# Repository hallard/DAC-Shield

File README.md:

0-10V DAC / ADC / RS485 and OLED Arduino Shield
===============================================

This is a simple board to be able to 
- Generate 4 0-10V analog output to drive industrial devices
- 2 0-10V analog input (unprotected) 
- A RS485 Driver (use RX/TX of Arduino)
- 2 I2C Oled connector (Adafruit or Tindie Oled)
- 1 Rotary Encoder
- 1 WS2812B RGB Led

<strike>This is a proto board, I've just ordered one on OSHPark, will put 
more details once received and tested</strike> This shield has been fully tested and it's working fine on all features. 
The only problem was my bad datasheet reading, the DAC7565 output from the chip are not 0V 5V as I expected but 0V 2.5V (internal VREF) So as I multiply ouput per 2, the output for these 4 outputs are 0V-5V not 0V-10V, you can change the multiplier by changing resitor R2/R4/R6/R8 from 10K to 30K.
Also TL072 are not working well with single rail supply for PWM to DAC conversion at low level (says from 0V to 1V), I replaced them
by LM358 (same package) but more suited for single rail supply.

I wrote an Arduino Library to drive the DAC7565 [here][3]

Check out news and other projects on my [blog][4]

Detailed Description
====================

Everything will be documented on my [blog][4]

**Schematic**  

**Board**  

&nbsp;&nbsp;

[3]: https://github.com/hallard/DAC7565
[4]: http://hallard.me

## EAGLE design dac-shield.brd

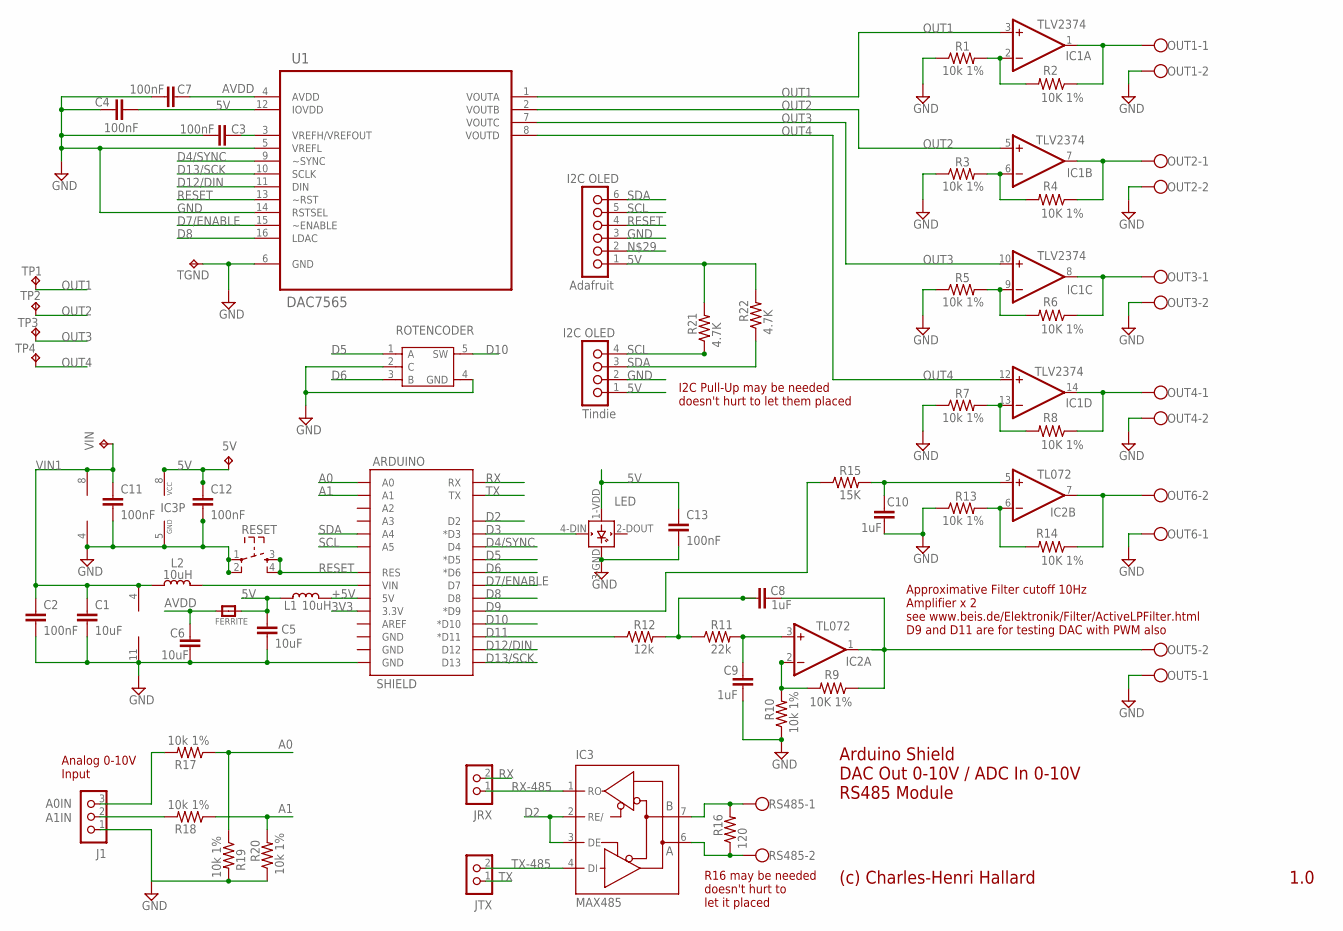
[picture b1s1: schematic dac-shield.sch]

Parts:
5V: TPPAD1-13; P1-13
ARDUINO: SHIELD; DUEMILANOVE_SHIELD_NOHOLES
C1, C5, C6: 10uF; 0805-CAP
C2, C3, C4, C7, C11, C12, C13: 100nF; 0805-CAP
C8, C9, C10: 1uF; 0805-CAP
FERRITE: FERRITE_0603; _0603
IC1: TLV2374; SO14
IC2: TL072; SO08
IC3: MAX485; SO08
J1: CON_HEADER_1X03-PTH; M1X3
JRX: CON_HEADER_1X02-PTH; M1X2
JTX: CON_HEADER_1X02-PTH; M1X2
L1, L2: 10uH; _0805
LED: WS2812B
OUT1, OUT2, OUT3, OUT4, OUT5, OUT6: CON-CLAMP-2; W237-102
R1, R3, R5, R7, R10, R13, R17, R18, R19, R20: 10k 1%; 0805-RES
R2, R4, R6, R8, R9, R14: 10K 1%; 0805-RES
R11: 22k; 0805-RES
R12: 12k; 0805-RES
R15: 15K; 0805-RES
R16: 120; 0805-RES
R21, R22: 4.7K; 0805-RES
RESET: SW_TACT_4P; SW_TACT_SMALL
ROTENCODER: ROTARY-ENCODE-5P; 5P-13.75X11.7X6.5H
RS485: CON-CLAMP-2; W237-102
TGND: TPPAD1-13; P1-13
TP1, TP2, TP3, TP4: TPPAD1-13; P1-13
U1: DAC7565; SOP65P640X120-16N
U$1: OLED_I2C_ADAFRUIT; 1X06_LOCK
U$2: OLED_I2C_TINDIE; 1X04_LOCK
VIN: TPPAD1-13; P1-13

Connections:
3V3: ARDUINO.3.3V
5V: 5V.TP, C4.1, C5.1, C12.1, C13.1, FERRITE.1, IC3.8 (VCC), L1.1, LED.1-VDD (VDD), R21.2, R22.2, U1.12 (IOVDD), U$1.1 (VIN), U$2.1 (VCC)
+5V: ARDUINO.5V, L1.2
A0: ARDUINO.A0, R17.1, R19.1
A0IN: J1.3, R17.2
A1: ARDUINO.A1, R18.1, R20.2
A1IN: J1.2, R18.2
AVDD: C6.2, C7.1, FERRITE.2, U1.4 (AVDD)
D2: ARDUINO.D2, IC3.2 (RE/), IC3.3 (DE)
D3: ARDUINO.D3 (*D3), LED.4-DIN (DIN)
D4/SYNC: ARDUINO.D4, U1.9 (~SYNC)
D5: ARDUINO.D5 (*D5), ROTENCODER.1 (A)
D6: ARDUINO.D6 (*D6), ROTENCODER.3 (B)
D7/ENABLE: ARDUINO.D7, U1.15 (~ENABLE)
D8: ARDUINO.D8, U1.16 (LDAC)
D9: ARDUINO.D9 (*D9), R15.1
D10: ARDUINO.D10 (*D10), ROTENCODER.5 (SW)
D11: ARDUINO.D11 (*D11), R12.1
D12/DIN: ARDUINO.D12, U1.11 (DIN)
D13/SCK: ARDUINO.D13, U1.10 (SCLK)
GND: ARDUINO.GND@0 (GND), C1.2, C2.2, C3.2, C4.2, C5.2, C6.1, C7.2, C9.1, C10.1, C11.2, C12.2, C13.2, IC1.11 (V-), IC2.4 (V-), IC3.5 (GND), J1.1, LED.3-GND (GND), OUT1.2, OUT2.2, OUT3.2, OUT4.2, OUT5.1, OUT6.1, R1.1, R3.1, R5.1, R7.1, R10.1, R13.1, R19.2, R20.1, RESET.1, RESET.2, ROTENCODER.2 (C), ROTENCODER.4 (GND), TGND.TP, U1.5 (VREFL), U1.6 (GND), U1.14 (RSTSEL), U$1.3 (GND), U$2.2 (GND)
unnamed: IC1.6 (-IN), R3.2, R4.2
unnamed: IC1.2 (-IN), R1.2, R2.2
unnamed: IC1.1 (OUT), OUT1.1, R2.1
unnamed: ARDUINO.VIN, L2.2
unnamed: IC2.2 (-IN), R9.2, R10.2
unnamed: C3.1, U1.3 (VREFH/VREFOUT)
unnamed: IC2.6 (-IN), R13.2, R14.2
unnamed: C8.2, IC2.1 (OUT), OUT5.2, R9.1
unnamed: IC1.7 (OUT), OUT2.1, R4.1
unnamed: IC1.9 (-IN), R5.2, R6.2
unnamed: IC1.8 (OUT), OUT3.1, R6.1
unnamed: IC1.13 (-IN), R7.2, R8.2
unnamed: IC1.14 (OUT), OUT4.1, R8.1
unnamed: C8.1, R11.1, R12.2
unnamed: C9.2, IC2.3 (+IN), R11.2
unnamed: IC2.7 (OUT), OUT6.2, R14.1
unnamed: C10.2, IC2.5 (+IN), R15.2
unnamed: IC3.7 (B), R16.2, RS485.1
unnamed: IC3.6 (A), R16.1, RS485.2
OUT1: IC1.3 (+IN), TP1.TP, U1.1 (VOUTA)
OUT2: IC1.5 (+IN), TP2.TP, U1.2 (VOUTB)
OUT3: IC1.10 (+IN), TP3.TP, U1.7 (VOUTC)
OUT4: IC1.12 (+IN), TP4.TP, U1.8 (VOUTD)
RESET: ARDUINO.RES, RESET.3, RESET.4, U1.13 (~RST), U$1.4 (RST)
RX: ARDUINO.RX, JRX.2
RX-485: IC3.1 (RO), JRX.1
SCL: ARDUINO.A5, R21.1, U$1.5 (SCL), U$2.4 (SCL)
SDA: ARDUINO.A4, R22.1, U$1.6 (SDA), U$2.3 (SDA)
TX: ARDUINO.TX, JTX.1
TX-485: IC3.4 (DI), JTX.2
VIN1: C1.1, C2.1, C11.1, IC1.4 (V+), IC2.8 (V+), L2.1, VIN.TP

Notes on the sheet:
Approximative Filter cutoff 10Hz Amplifier x 2 see www.beis.de/Elektronik/Filter/ActiveLPFilter.html D9 and D11 are for testing DAC with PWM also
I2C Pull-Up may be needed doesn't hurt to let them placed
Analog 0-10V Input
(c) Charles-Henri Hallard
1.0
Arduino Shield DAC Out 0-10V / ADC In 0-10V RS485 Module
R16 may be needed doesn't hurt to let it placed

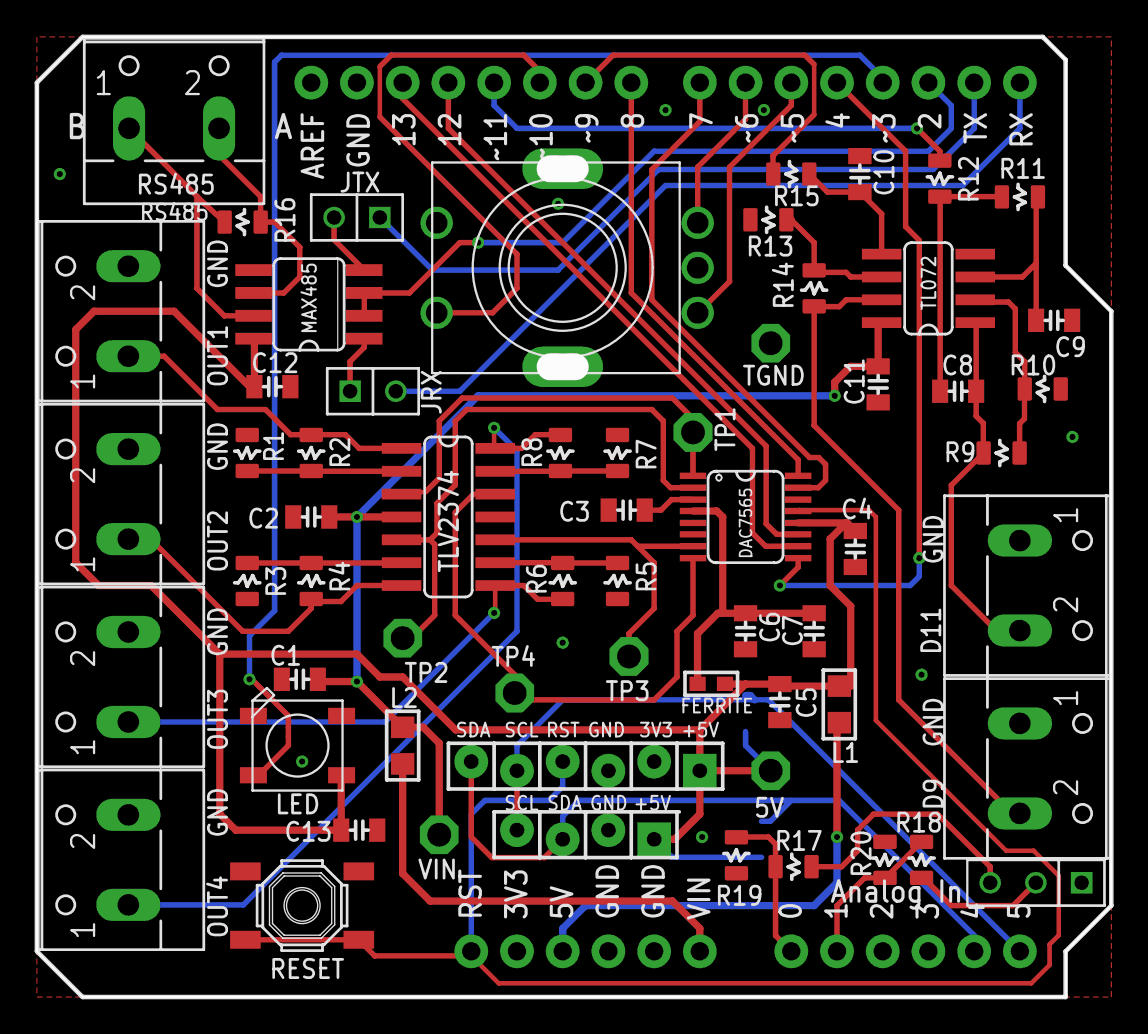
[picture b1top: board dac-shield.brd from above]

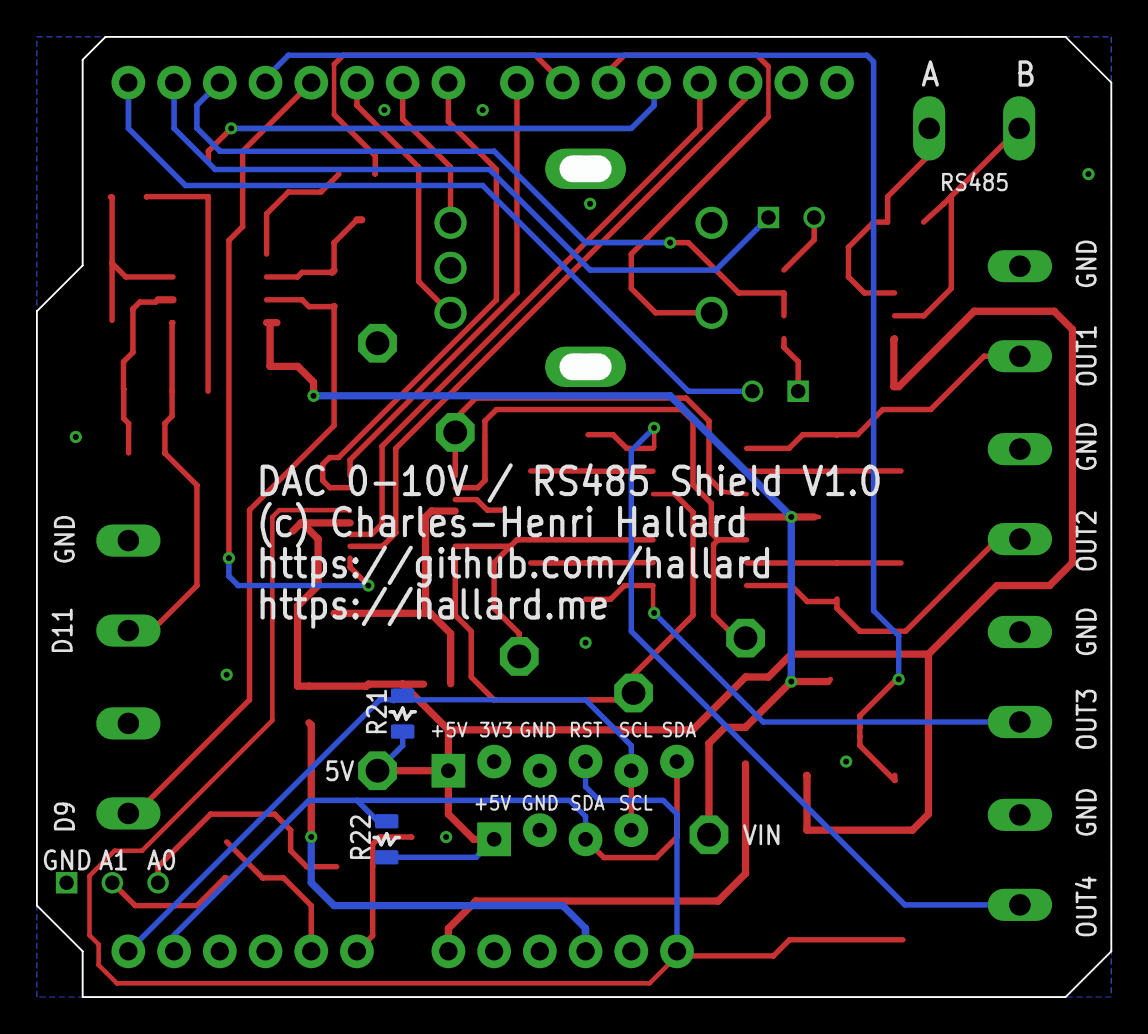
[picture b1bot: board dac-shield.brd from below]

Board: 2 copper layers, 58.3 x 51.9 mm, 65 parts (2 on the bottom side), 51 nets.

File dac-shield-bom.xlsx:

Qty | Value | Device | Package | Parts | Description | MPN | PACKAGE | SUPPLIER
7 |  | Clamp Connector | W237-102 | OUT1, OUT2, OUT3, OUT4, OUT5, OUT6, RS485 | WAGO SCREW CLAMP
1 |  | Ferrite | _0603 | FERRITE | Ferrite Bead
1 |  | Rotary Encoder | 5P-13.75X11.7X6.5H | ROTENCODER | Rotary Encode With Switch
1 |  | Tactile Switch | SW_TACT_SMALL | RESET | Switch
7 | 100nF | CAP0805-CAP | 0805-CAP | C2, C3, C4, C7, C11, C12, C13 | Capacitor
6 | 10K 1% | RESISTOR0805-RES | 0805-RES | R2, R4, R6, R8, R9, R14 | Resistor
10 | 10k 1% | RESISTOR0805-RES | 0805-RES | R1, R3, R5, R7, R10, R13, R17, R18, R19, R20 | Resistor
3 | 10uF | CAP0805-CAP | 0805-CAP | C1, C5, C6 | Capacitor
2 | 10uH | INDUCTOR_0805 | _0805 | L1, L2 | Inductors
1 | 120 | RESISTOR0805-RES | 0805-RES | R16 | Resistor
1 | 12k | RESISTOR0805-RES | 0805-RES | R12 | Resistor
1 | 15K | RESISTOR0805-RES | 0805-RES | R15 | Resistor
3 | 1uF | CAP0805-CAP | 0805-CAP | C8, C9, C10 | Capacitor
1 | 22k | RESISTOR0805-RES | 0805-RES | R11 | Resistor
2 | 4.7K | RESISTOR0805-RES | 0805-RES | R21, R22 | Resistor
1 | DAC7565 | DAC7565IAPW | SOP65P640X120-16N | U1 | DAC | DAC7565IAPW | TSSOP-16 | Texas Instruments
1 | MAX485 | MAX485CSA | SO08 | IC3 | RS485 TRANSEIVER | MAX485CSA |  | MAXIM
1 | TL072 | TL072D | SO08 | IC2 | DUAL OP AMP
1 | TLV2374 | LM324D | SO14 | IC1 | QUAD OP AMP
1 | WS2812B | WS2812B | WS2812B / 4 PINS Version | LED

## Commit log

2014-01-29 Creation
2014-01-29 Image Link Case change
2014-01-29 Image Link Case Error
2014-01-29 Deleted Backup File
2014-09-10 Changed Via Mask
    Changed Via Stop Limit to avoid copper on via
2014-09-10 Updated to Eagle 6.6
2015-04-19 Added Testing results and Arduino Lib
2015-04-19 Change TL072 by LM358

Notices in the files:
parts and their libraries:
SparkFun-Boards: Licensing: CC v3.0 Share-Alike You are welcome to use this library for commercial purposes.
microbuilder: This work is placed in the public domain, and may be freely used for commercial and non-commercial work with the following conditions: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
